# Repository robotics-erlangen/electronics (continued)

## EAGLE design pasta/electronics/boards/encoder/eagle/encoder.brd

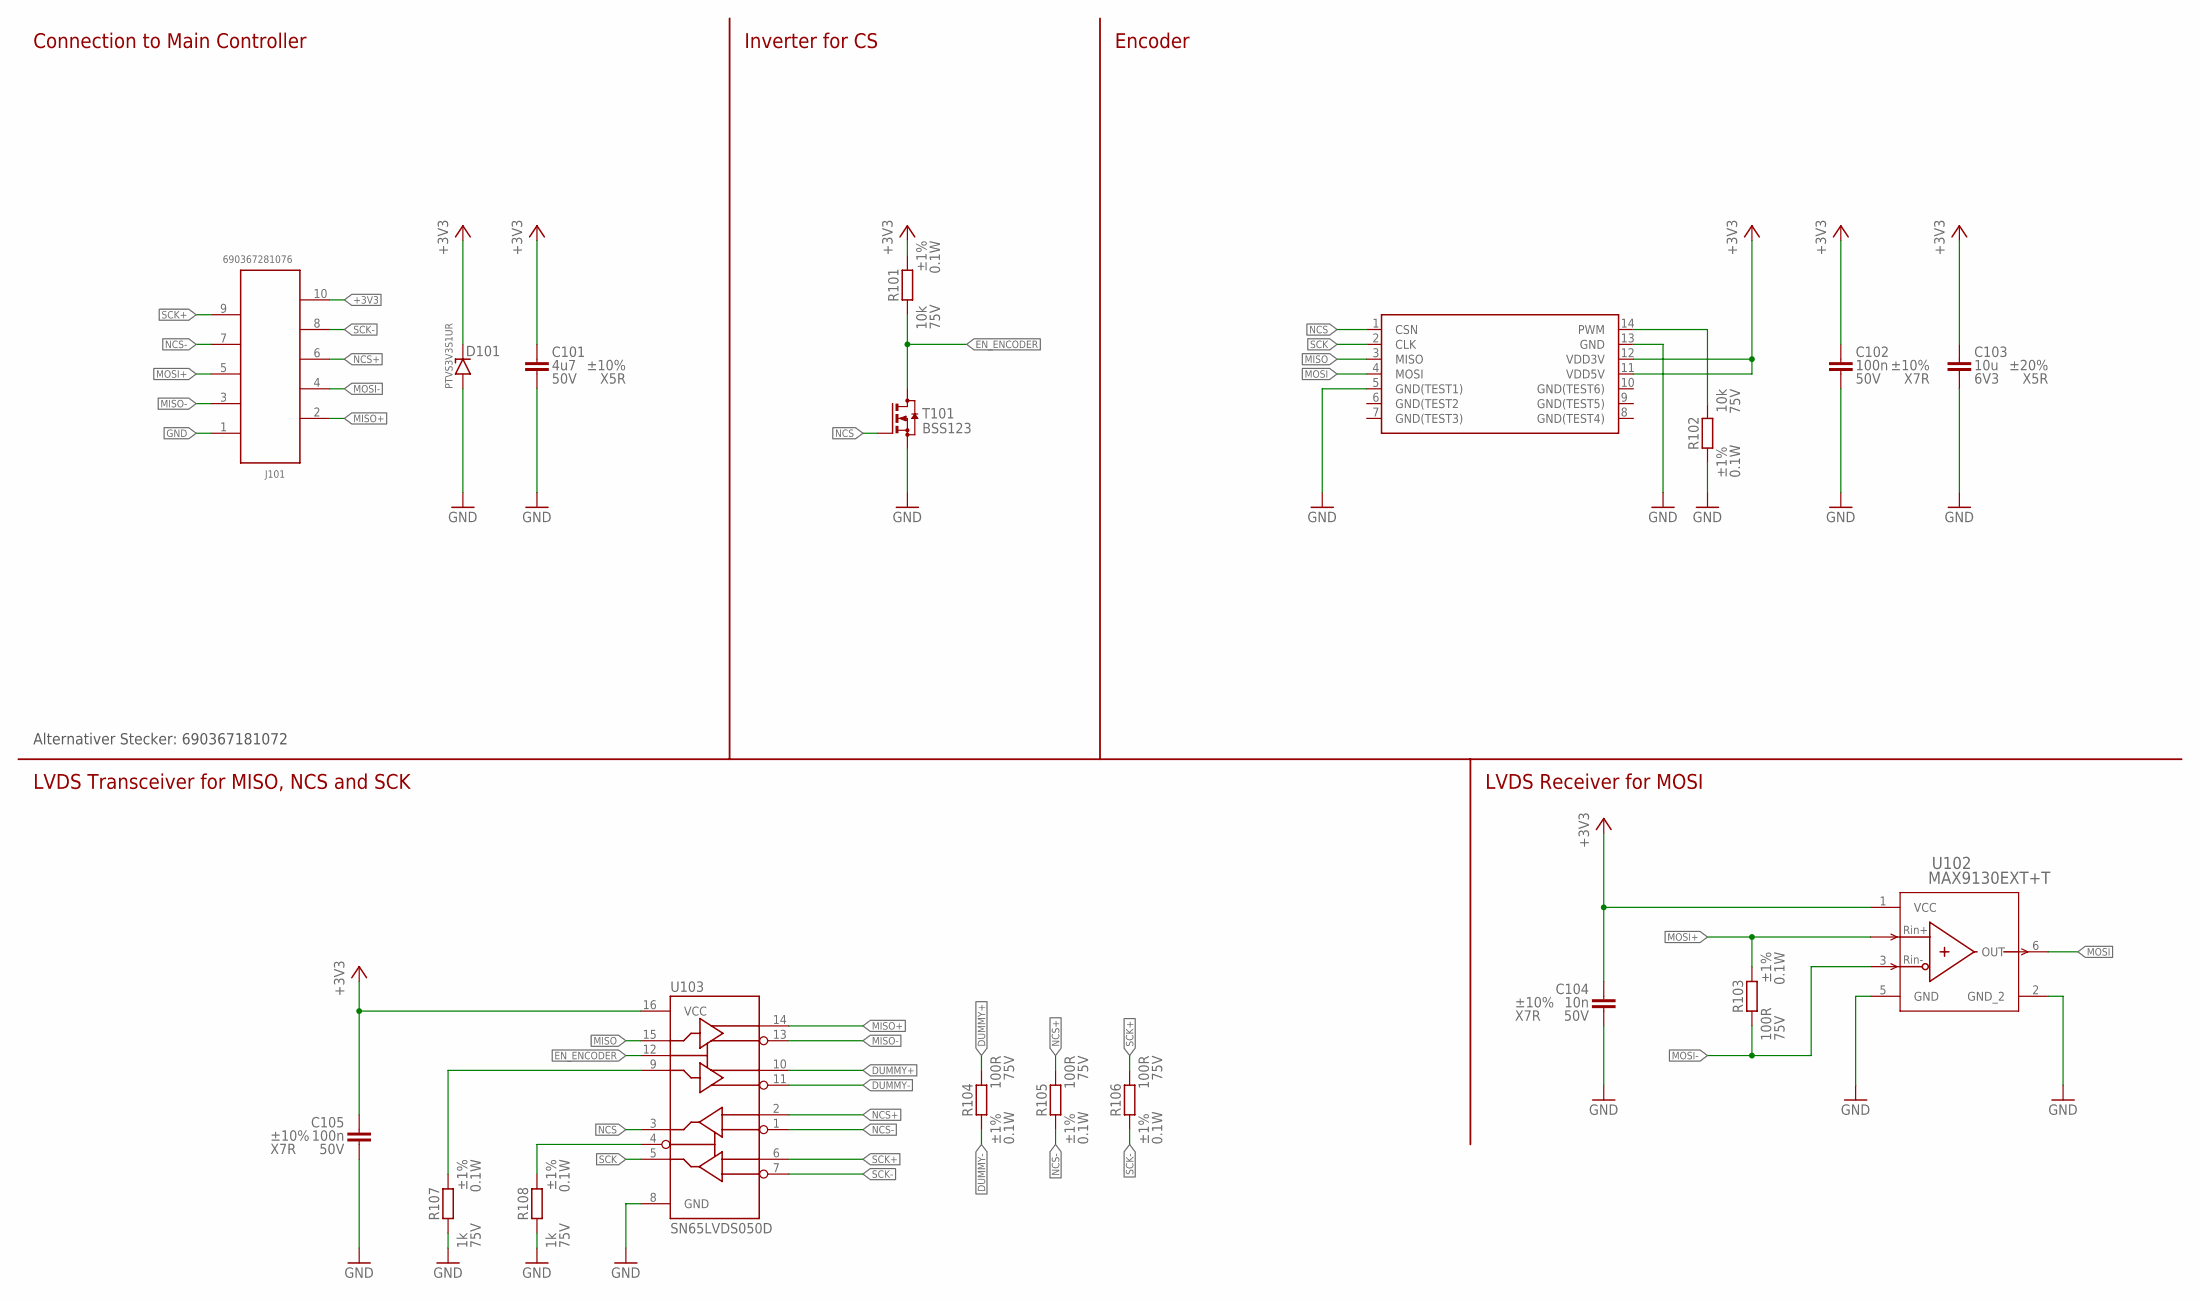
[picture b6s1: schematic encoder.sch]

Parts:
C101: 4u7 6V3; C0805
C102, C105: 100n 6V3; C0603
C103: 10u 6V3; C0603
C104: 10n 50V; C0603
D101: PTVS3V3S1UR; SOD123
J101: 690367281076; MPN 690367281076
R101, R102: 10k; R0603
R103, R104, R105, R106: 100R; R0603
R107, R108: 1k; R0603
T101: BSS123; SOT23-3
U101: AS5048A-HTSP
U102: MAX9130EXT+T; 21-0077G_MXM
U103: SN65LVDS050D; SOIC-16

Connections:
+3V3: C101.1, C102.1, C103.1, C104.1, C105.1, D101.C (KATHODE), J101.10 (1), R101.2, U101.11 (VDD5V), U101.12 (VDD3V), U102.1 (VCC), U103.16 (VCC)
DUMMY+: R104.1, U103.10 (2Y)
DUMMY-: R104.2, U103.11 (2Z)
EN_ENCODER: R101.1, T101.3 (D), U103.12 (DE)
GND: C101.2, C102.2, C103.2, C104.2, C105.2, D101.A (ANODE), J101.1 (10), R102.2, R107.1, R108.1, T101.2 (S), U101.5 (GND(TEST1)), U101.13 (GND), U102.2 (GND_2), U102.5 (GND), U103.8 (GND)
MISO: U101.3 (MISO), U103.15 (1D)
MISO+: J101.2 (9), U103.14 (1Y)
MISO-: J101.3 (8), U103.13 (1Z)
MOSI: U101.4 (MOSI), U102.6 (OUT)
MOSI+: J101.5 (6), R103.2, U102.4 (IN+)
MOSI-: J101.4 (7), R103.1, U102.3 (IN-)
unnamed: R102.1, U101.14 (PWM)
unnamed: R108.2, U103.4 (RE)
unnamed: R107.2, U103.9 (2D)
NCS: T101.1 (G), U101.1 (CSN), U103.3 (1R)
NCS+: J101.6 (5), R105.1, U103.2 (1A)
NCS-: J101.7 (4), R105.2, U103.1 (1B)
SCK: U101.2 (CLK), U103.5 (2R)
SCK+: J101.9 (2), R106.1, U103.6 (2A)
SCK-: J101.8 (3), R106.2, U103.7 (2B)

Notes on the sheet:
Alternativer Stecker: 690367181072
Connection to Main Controller
Inverter for CS
Encoder
LVDS Transceiver for MISO, NCS and SCK
LVDS Receiver for MOSI

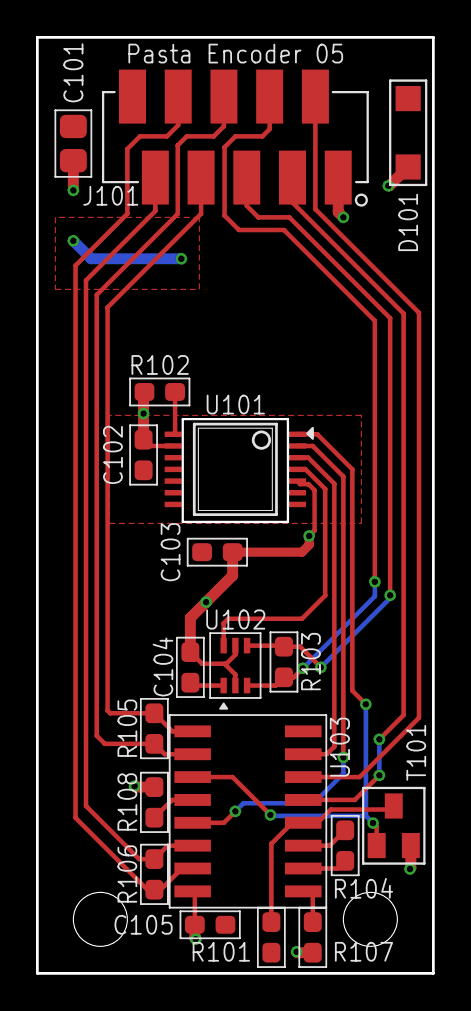
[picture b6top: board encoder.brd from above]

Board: 2 copper layers, 22.0 x 52.0 mm, 19 parts (0 on the bottom side), 20 nets.

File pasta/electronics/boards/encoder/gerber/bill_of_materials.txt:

Stückliste exportiert aus D:/hardware/pasta/electronics/boards/encoder/eagle/encoder.sch am 04.07.2023 16:03

Part Value        Device                Package      Description                                                                                      CAPACITANCE COPYRIGHT                                                DIELECTRIC MF                        MOUSER               MPN               POWER RESISTANCE TOLERANCE VOLTAGE
C101 4u7 6V3      C(4.7UF,50V,0805)     C0805        Robotics Erlangen Capacitor Library                                                              4u7                                                                  X5R        Samsung                                        CL21A475KBQNNNE                    ±10%      50V    
C102 100n 6V3     C(100NF,50V,0603)     C0603        Robotics Erlangen Capacitor Library                                                              100n                                                                 X7R        Würth Elektronik                               885012206095                       ±10%      50V    
C103 10u 6V3      C(10UF,6.3V,0603)     C0603        Robotics Erlangen Capacitor Library                                                              10u                                                                  X5R        Würth Elektronik                               885012106006                       ±20%      6V3    
C104 10n 50V      C(10NF,50V,0603)      C0603        Robotics Erlangen Capacitor Library                                                              10n                                                                  X7R        Würth Elektronik                               885012206089                       ±10%      50V    
C105 100n 6V3     C(100NF,50V,0603)     C0603        Robotics Erlangen Capacitor Library                                                              100n                                                                 X7R        Würth Elektronik                               885012206095                       ±10%      50V    
D101 PTVS3V3S1UR  PTVS3V3S1UR           SOD123                                                                                                                                                                                        Nexperia                  771-PTVS3V3S1UR115    PTVS3V3S1UR,115                                    
J101 690367281076 690367281076          690367281076 WR-MM Female SMT Connector with Polarization, 10 Pins=>Code : Con_BTB_MM_Female_SMT_690367281076                                                                                 Würth Elektronik                               690367281076                                        
R101 10k          R(10K,75V,0.1W,0603)  R0603        Robotics Erlangen Resistor Library                                                                                                                                               YAGEO                                          RC0603FR-0710KL   0.1W  10k        ±1%       75V    
R102 10k          R(10K,75V,0.1W,0603)  R0603        Robotics Erlangen Resistor Library                                                                                                                                               YAGEO                                          RC0603FR-0710KL   0.1W  10k        ±1%       75V    
R103 100R         R(100R,75V,0.1W,0603) R0603        Robotics Erlangen Resistor Library                                                                                                                                               YAGEO                                          RC0603FR-07100RL  0.1W  100R       ±1%       75V    
R104 100R         R(100R,75V,0.1W,0603) R0603        Robotics Erlangen Resistor Library                                                                                                                                               YAGEO                                          RC0603FR-07100RL  0.1W  100R       ±1%       75V    
R105 100R         R(100R,75V,0.1W,0603) R0603        Robotics Erlangen Resistor Library                                                                                                                                               YAGEO                                          RC0603FR-07100RL  0.1W  100R       ±1%       75V    
R106 100R         R(100R,75V,0.1W,0603) R0603        Robotics Erlangen Resistor Library                                                                                                                                               YAGEO                                          RC0603FR-07100RL  0.1W  100R       ±1%       75V    
R107 1k           R(1.0K,75V,0.1W,0603) R0603        Robotics Erlangen Resistor Library                                                                                                                                               YAGEO                                          RC0603FR-071KL    0.1W  1k         ±1%       75V    
R108 1k           R(1.0K,75V,0.1W,0603) R0603        Robotics Erlangen Resistor Library                                                                                                                                               YAGEO                                          RC0603FR-071KL    0.1W  1k         ±1%       75V    
T101 BSS123       BSS123                SOT23-3      N-CHANNEL MOS FET                                                                                                                                                                Nexperia                  726-BSS123NH6327XTSA BSS123NH6327XTSA1                                   
U101 AS5048A-HTSP AS5048A-HTSP          AS5048A-HTSP                                                                                                                                                                                  ams                       985-AS5048A-HTSP-500 AS5048A-HTSP                                        
U102 MAX9130EXT+T MAX9130EXT+T          21-0077G_MXM                                                                                                              Copyright (C) 2021 Ultra Librarian. All rights reserved.            Maxim Integrated Products                      MAX9130EXT+T                                        
U103 SN65LVDS050D SN65LVDS050D          SOIC-16                                                                                                                                                                                       Texas Instruments                              SN65LVDS050D

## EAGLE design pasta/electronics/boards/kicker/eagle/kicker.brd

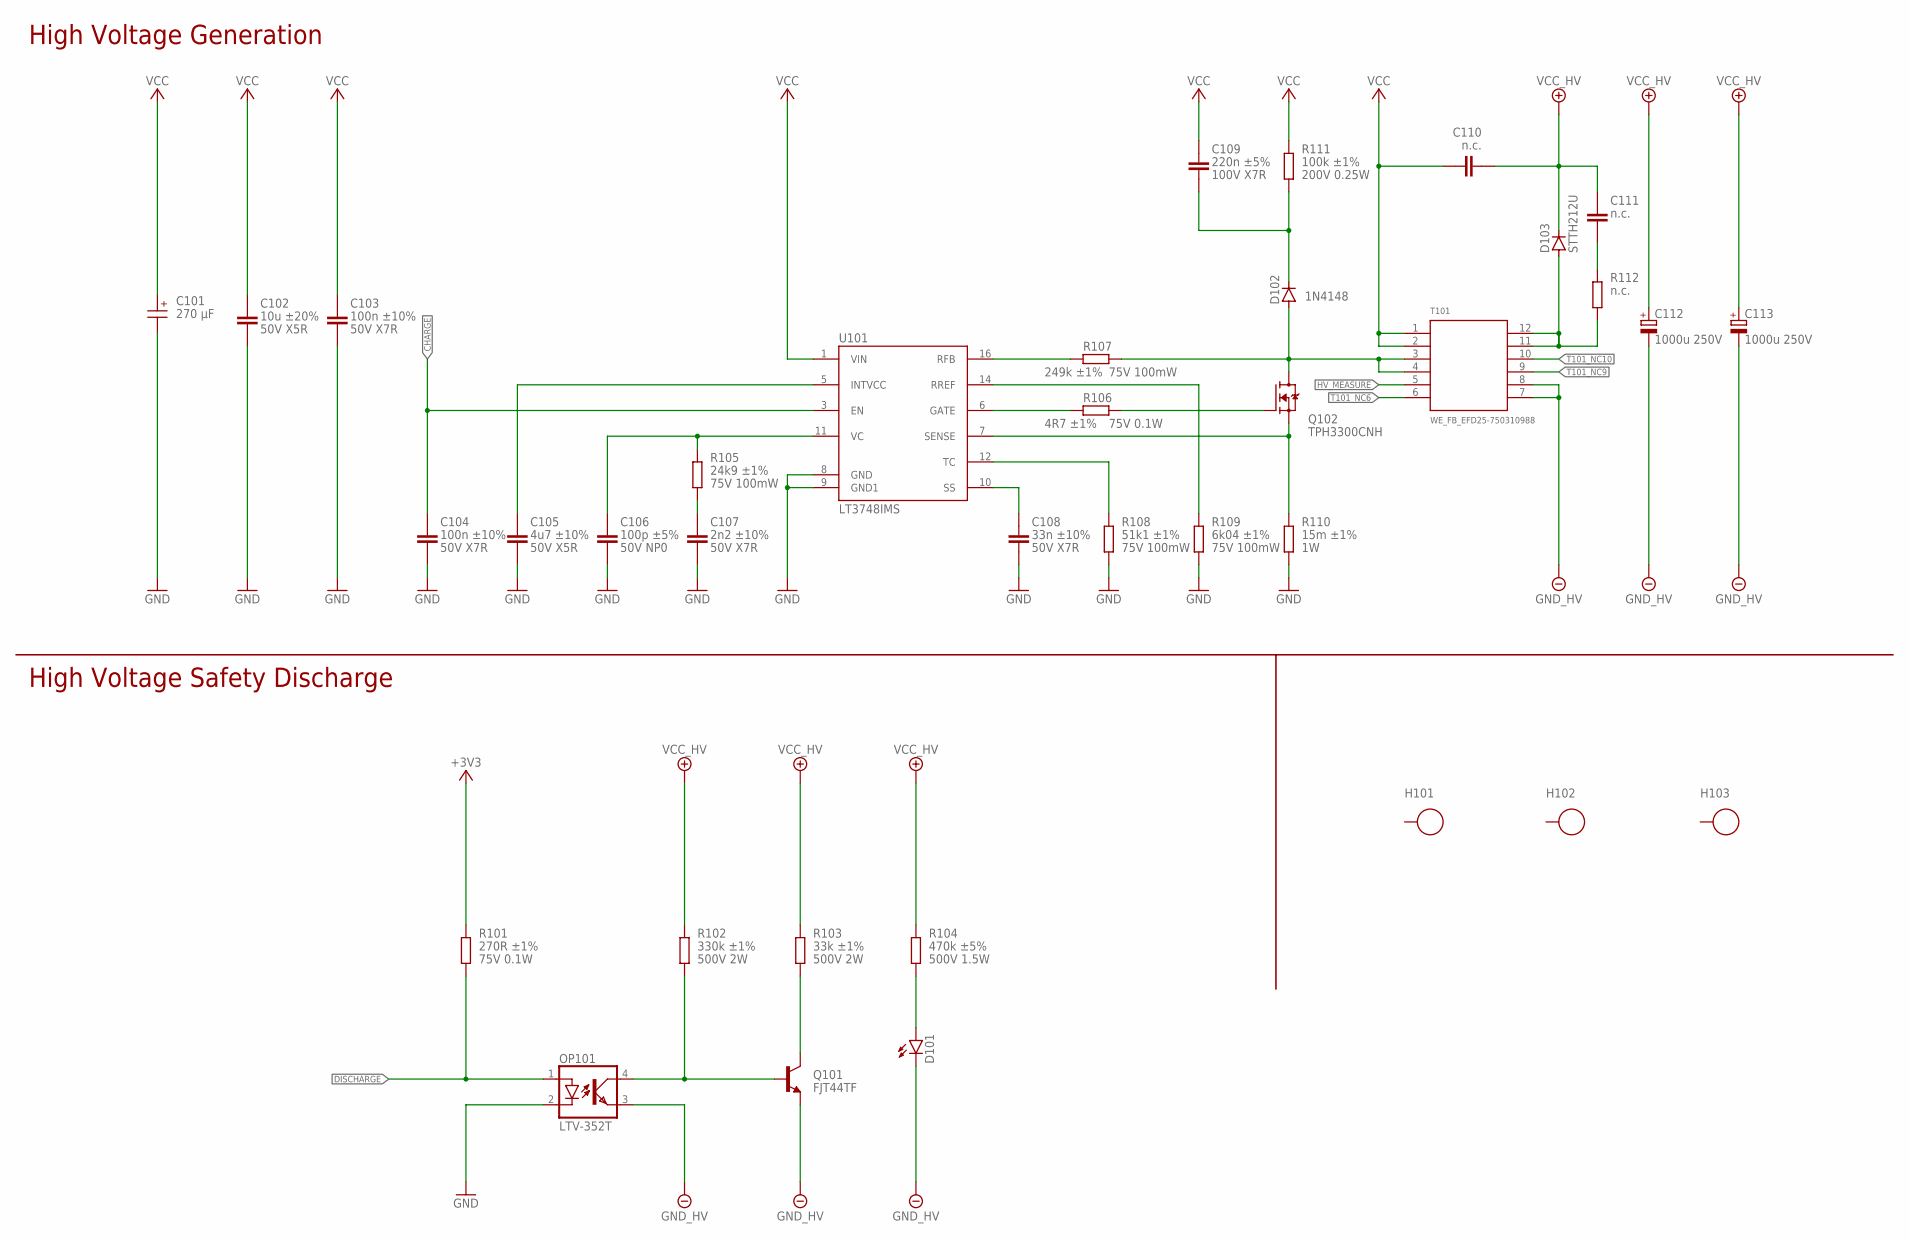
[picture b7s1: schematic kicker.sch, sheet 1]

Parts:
C101: 270 µF; WCAP-PSLC_10X12.4(DXL)
C102: 10u ±20% 50V X5R; C1206
C103, C104: 100n ±10% 50V X7R; C0603
C105: 4u7 ±10% 50V X5R; C0805
C106: 100p ±5% 50V NP0; C0603
C107: 2n2 ±10% 50V X7R; C0603
C108: 33n ±10% 50V X7R; C0603
C109: C(1210); C1210; TOLERANCE ±5%; VOLTAGE 100V; MPN C0805C224J1RECTU
C110, C111: n.c.; C1206
C112, C113: 1000u 250V; ESMQ251VSN102MQ45S
D101: LED5MM
D102: 1N4148; SOD-123
D103: STTH212U; SMB
H101, H102, H103: 9774060360R; 9774***360
OP101: LTV-352T; DIL4-SMD
Q101: FJT44TF; SOT223
Q102: TPH3300CNH; SOP-8
R101: 270R ±1% 75V 0.1W; R0603
R102: R(2512); R2512; TOLERANCE ±1%; VOLTAGE 500V; MPN CRGP2512F330K
R103: R(2512); R2512; TOLERANCE 1%; VOLTAGE 500V; MPN CRGP2512F33K
R104: R(2512); R2512; TOLERANCE ±5%; VOLTAGE 500V; MPN CRCW2512470KJNEGHP
R105: R(0603); R0603; TOLERANCE ±1%; VOLTAGE 75V; MPN RE0603FRE0724K9L
R106: 4R7 ±1% 75V 0.1W; R0603
R107: R(0603); R0603; TOLERANCE ±1%; VOLTAGE 75V; MPN RC0603FR-07249KL
R108: R(0603); R0603; TOLERANCE ±1%; VOLTAGE 75V; MPN RC0603FR-0751K1L
R109: R(0603); R0603; TOLERANCE ±1%; VOLTAGE 75V; MPN AC0603FR-136K04L
R110: R(1206); R1206; TOLERANCE ±1%; MPN ERJ-8BWFR015V
R111: 100k ±1% 200V 0.25W; R1206
R112: n.c.; R1206
T101: WE_FB_EFD25-750310988; WE_FB_EFD25
U101: LT3748IMS; MSOP16

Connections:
+3V3: R101.2; also elsewhere on the board
CHARGE: C104.1, U101.3 (EN); also elsewhere on the board
DISCHARGE: OP101.1 (A), R101.1; also elsewhere on the board
GND: C101.2 (-), C102.2, C103.2, C104.2, C105.2, C106.2, C107.2, C108.2, OP101.2 (C), R108.1, R109.1, R110.1, U101.8 (GND), U101.9 (GND1); also elsewhere on the board
GND_HV: C112.N (-), C113.N (-), D101.K (C), OP101.3 (EMIT), Q101.3 (E), T101.7, T101.8; also elsewhere on the board
HV_MEASURE: T101.5
unnamed: R108.2, U101.12 (TC)
unnamed: D103.A, R112.1, T101.11, T101.12
unnamed: R109.2, U101.14 (RREF)
unnamed: C108.1, U101.10 (SS)
unnamed: D101.A, R104.1
unnamed: C109.2, D102.C, R111.1
unnamed: Q102.1 (S), Q102.2 (S), Q102.3 (S), R110.2, U101.7 (SENSE)
unnamed: C105.1, U101.5 (INTVCC)
unnamed: C106.1, R105.2, U101.11 (VC)
unnamed: C107.1, R105.1
unnamed: Q102.4 (G), R106.1
unnamed: R106.2, U101.6 (GATE)
unnamed: R107.2, U101.16 (RFB)
unnamed: C111.2, R112.2
unnamed: OP101.4 (COL), Q101.1 (B), R102.1
unnamed: Q101.2 (C), Q101.4 (C), R103.1
T101_NC6: T101.6
T101_NC9: T101.9
T101_NC10: T101.10
TRAFO: D102.A, Q102.5 (D), R107.1, T101.3, T101.4
VCC: C101.1 (+), C102.1, C103.1, C109.1, C110.1, R111.2, T101.1, T101.2, U101.1 (VIN); also elsewhere on the board
VCC_HV: C110.2, C111.1, C112.P (+), C113.P (+), D103.C, R102.2, R103.2, R104.2; also elsewhere on the board

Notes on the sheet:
High Voltage Generation
High Voltage Safety Discharge

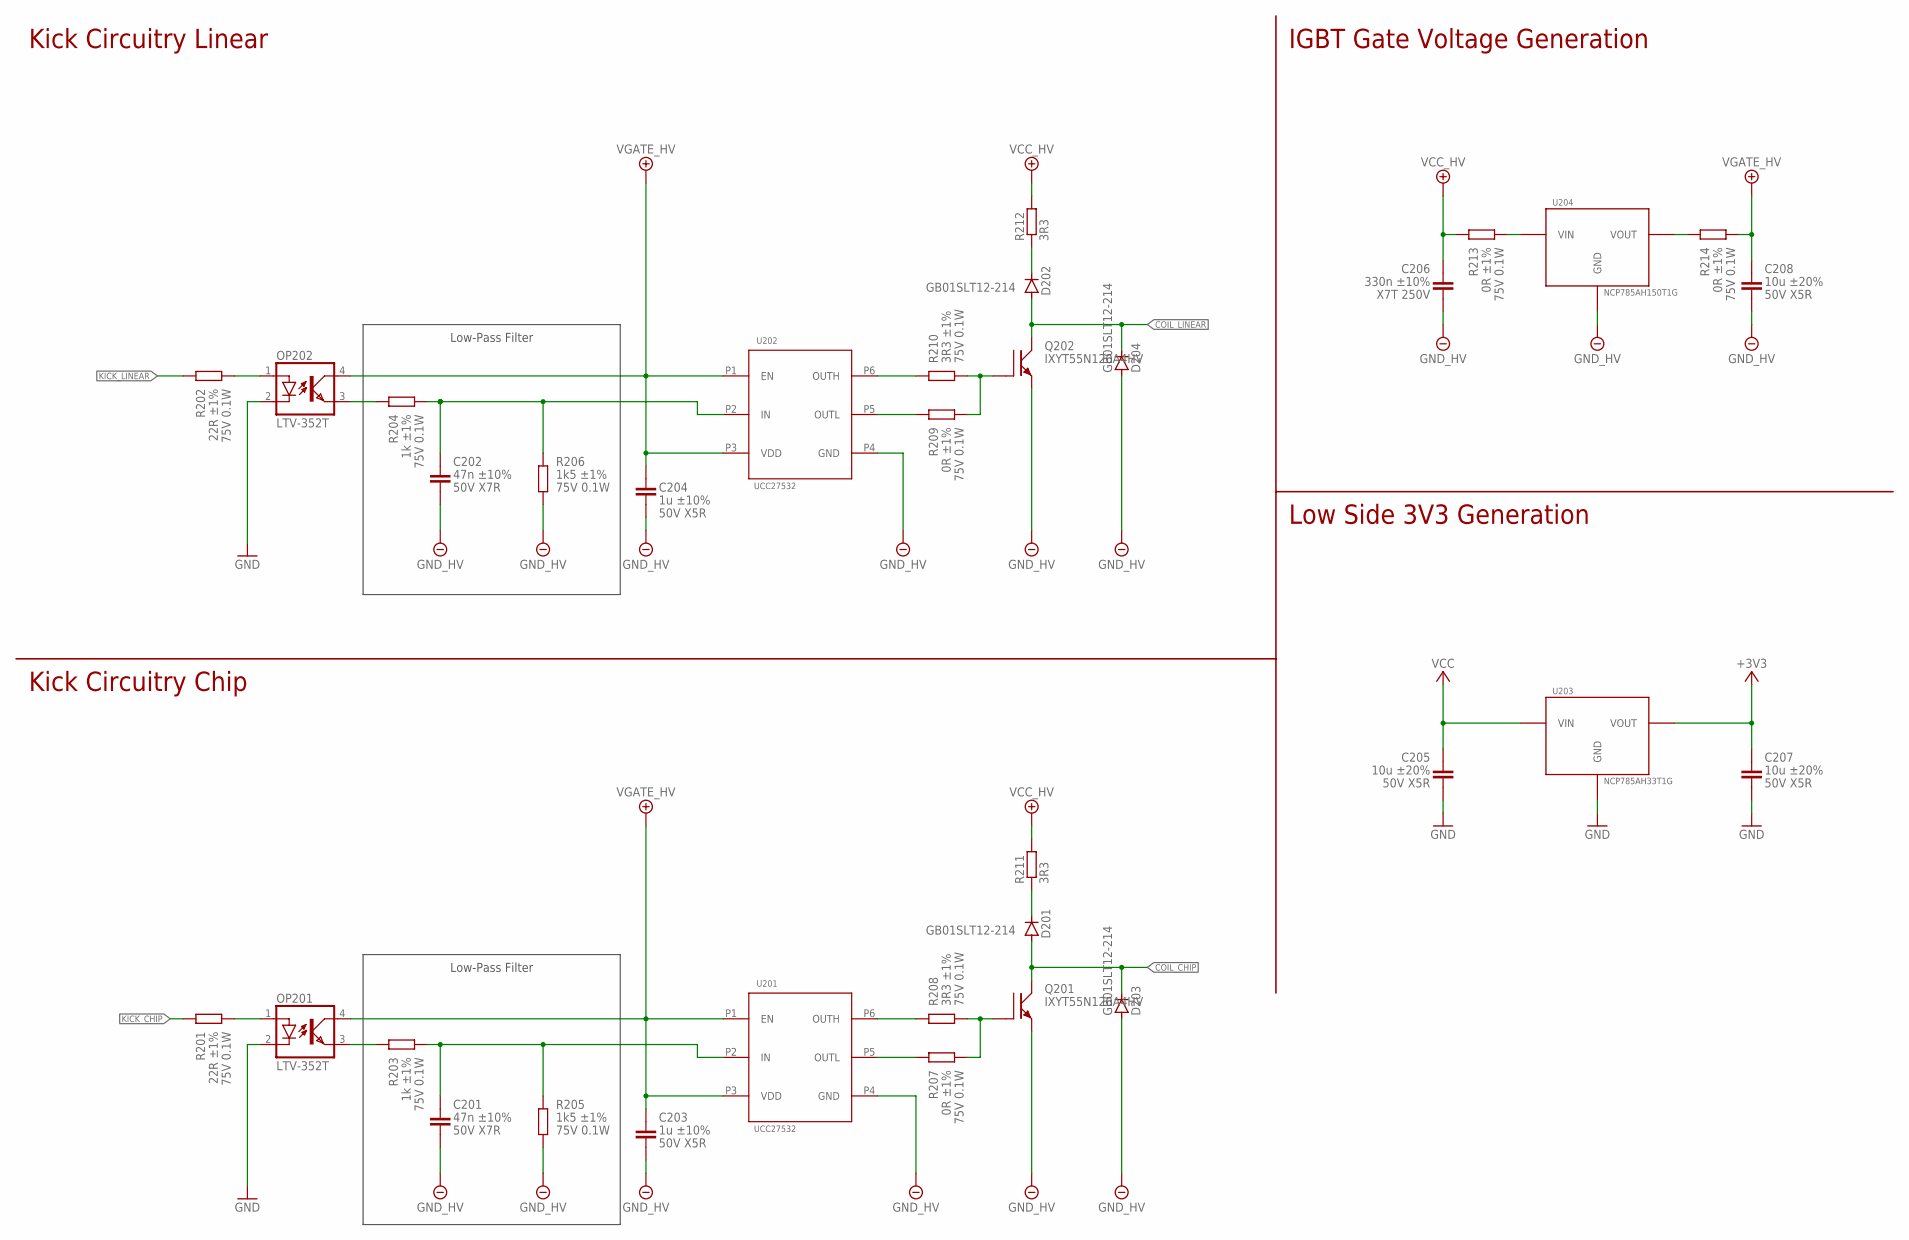
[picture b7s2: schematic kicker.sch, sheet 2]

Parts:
C201, C202: 47n ±10% 50V X7R; C0603
C203, C204: 1u ±10% 50V X5R; C0603
C205, C207, C208: 10u ±20% 50V X5R; C1206
C206: C(1210); C1210; TOLERANCE ±10%; VOLTAGE 250V; MPN C3225X7T2E334K200AA
D201, D202, D203, D204: GB01SLT12-214; DO-214
OP201, OP202: LTV-352T; DIL4-SMD
Q201, Q202: IXYT55N120A4HV; TO-268HV
R201, R202: 22R ±1% 75V 0.1W; R0603
R203, R204: 1k ±1% 75V 0.1W; R0603
R205, R206: 1k5 ±1% 75V 0.1W; R0603
R207, R209, R213, R214: 0R ±1% 75V 0.1W; R0603
R208, R210: 3R3 ±1% 75V 0.1W; R0603
R211, R212: 3R3; R4527
U201, U202: UCC27532; SOT23-6
U203: NCP785AH33T1G; NCP785AH*T1G
U204: NCP785AH150T1G; NCP785AH*T1G

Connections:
+3V3: C207.1, U203.3 (VOUT); also elsewhere on the board
COIL_CHIP: D201.A, D203.C, Q201.3 (C); also elsewhere on the board
COIL_LINEAR: D202.A, D204.C, Q202.3 (C); also elsewhere on the board
GND: C205.2, C207.2, OP201.2 (C), OP202.2 (C), U203.2 (GND); also elsewhere on the board
GND_HV: C201.2, C202.2, C203.2, C204.2, C206.2, C208.2, D203.A, D204.A, Q201.1 (E), Q202.1 (E), R205.1, R206.1, U201.P4 (GND), U202.P4 (GND), U204.2 (GND); also elsewhere on the board
KICK_CHIP: R201.1; also elsewhere on the board
KICK_LINEAR: R202.1; also elsewhere on the board
unnamed: OP202.3 (EMIT), R204.1
unnamed: OP201.3 (EMIT), R203.1
unnamed: R213.2, U204.1 (VIN)
unnamed: R214.1, U204.3 (VOUT)
unnamed: R208.1, U201.P6 (OUTH)
unnamed: R210.1, U202.P6 (OUTH)
unnamed: R209.1, U202.P5 (OUTL)
unnamed: Q202.2 (G), R209.2, R210.2
unnamed: C202.1, R204.2, R206.2, U202.P2 (IN)
unnamed: R207.1, U201.P5 (OUTL)
unnamed: Q201.2 (G), R207.2, R208.2
unnamed: D202.C, R212.1
unnamed: OP201.1 (A), R201.2
unnamed: D201.C, R211.1
unnamed: C201.1, R203.2, R205.2, U201.P2 (IN)
unnamed: OP202.1 (A), R202.2
VCC: C205.1, U203.1 (VIN); also elsewhere on the board
VCC_HV: C206.1, R211.2, R212.2, R213.1; also elsewhere on the board
VGATE_HV: C203.1, C204.1, C208.1, OP201.4 (COL), OP202.4 (COL), R214.2, U201.P1 (EN), U201.P3 (VDD), U202.P1 (EN), U202.P3 (VDD); also elsewhere on the board

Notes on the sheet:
Kick Circuitry Linear
Kick Circuitry Chip
Low Side 3V3 Generation
IGBT Gate Voltage Generation
Low-Pass Filter

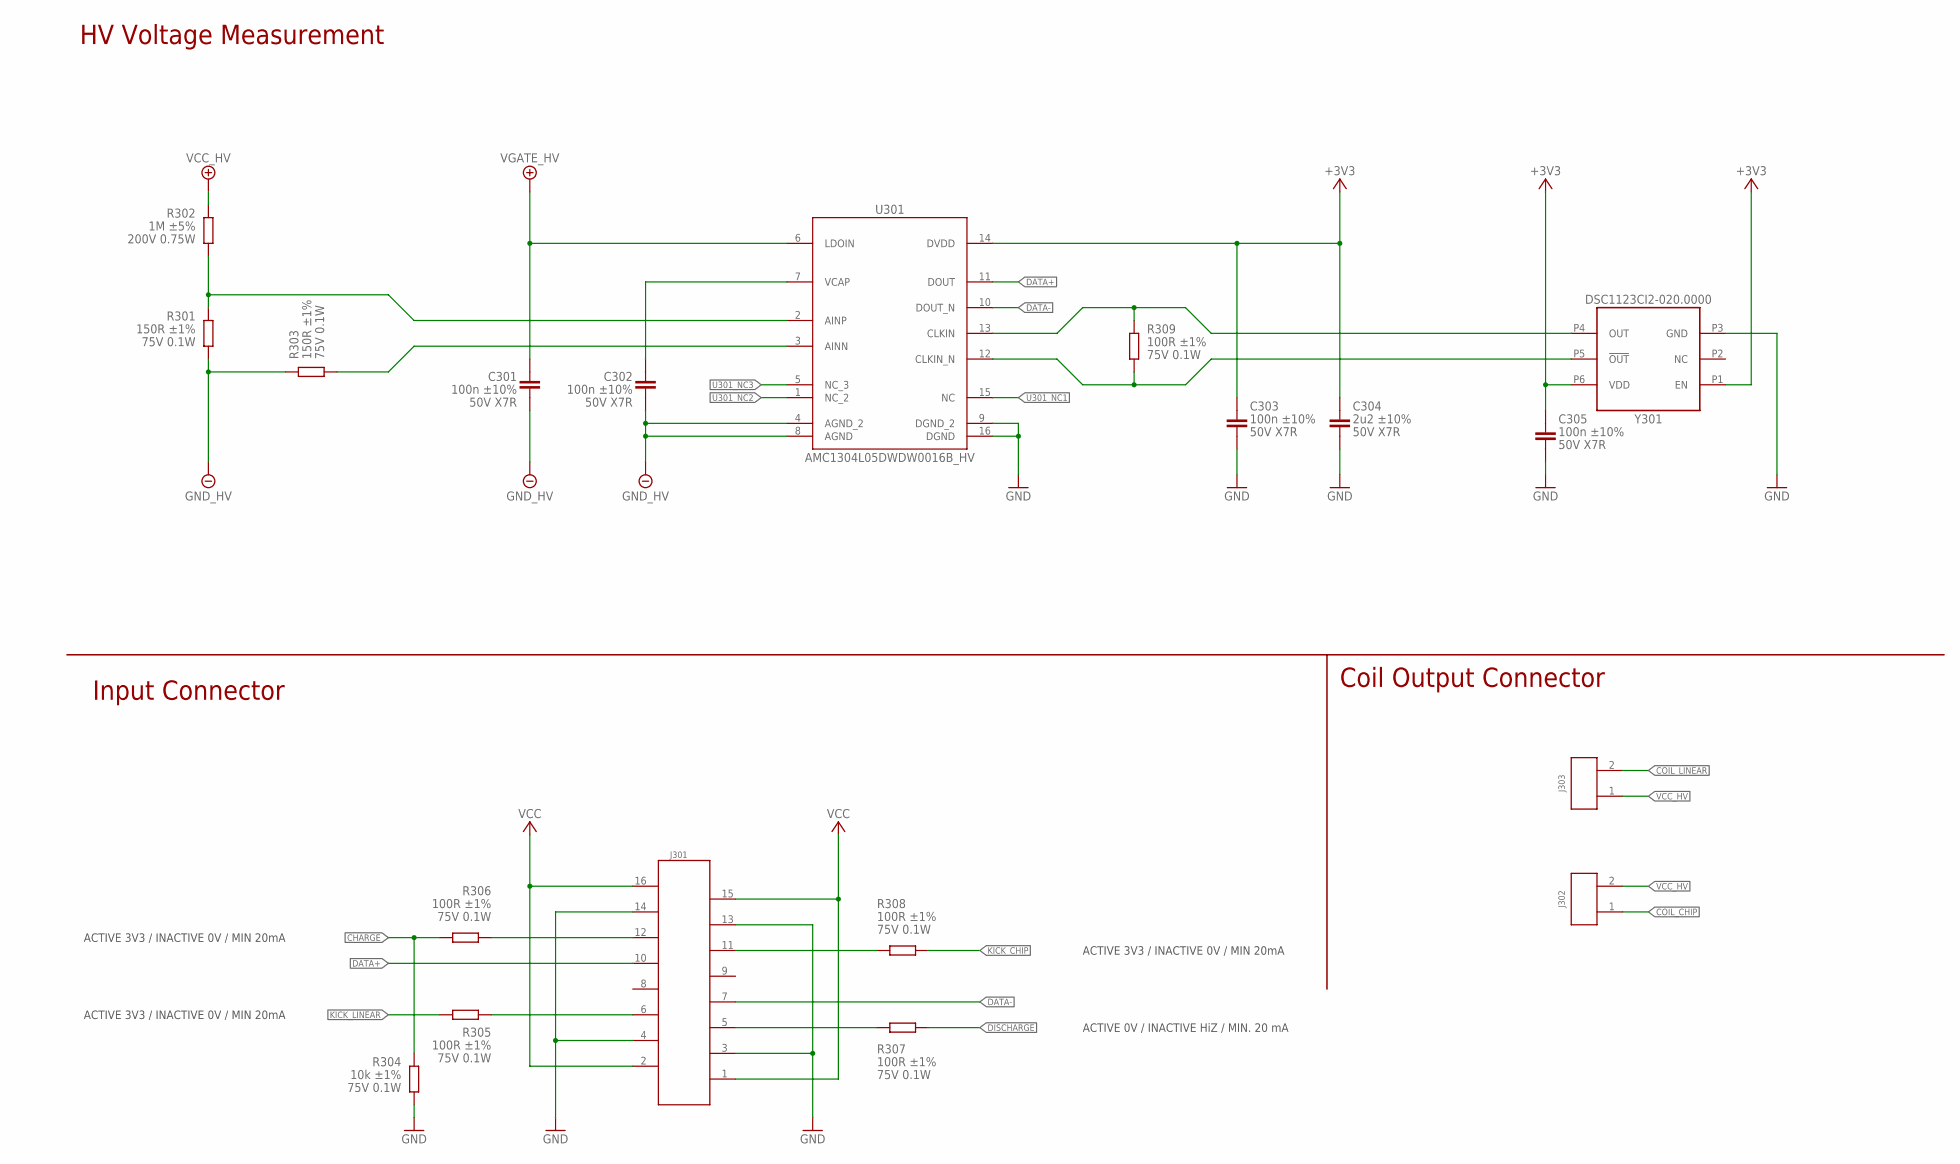
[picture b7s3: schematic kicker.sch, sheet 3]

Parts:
C301, C302, C303, C305: 100n ±10% 50V X7R; C0603
C304: 2u2 ±10% 50V X7R; C0805
J301: 690367181672
J302, J303: 66100311622; 66100311622*
R301, R303: 150R ±1% 75V 0.1W; R0603
R302: R(2010); R2010; TOLERANCE ±5%; VOLTAGE 200V; MPN RC2010JK-071ML
R304: 10k ±1% 75V 0.1W; R0603
R305, R306, R307, R308, R309: 100R ±1% 75V 0.1W; R0603
U301: AMC1304L05DWDW0016B_HV; DW0016B_HV
Y301: DSC1123CI2-020.0000; DSC11X3

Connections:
+3V3: C303.1, C304.1, C305.1, U301.14 (DVDD), Y301.P1 (EN), Y301.P6 (VDD); also elsewhere on the board
CHARGE: R304.2, R306.2; also elsewhere on the board
CLK-: R309.1, U301.12 (CLKIN_N), Y301.P5 (!OUT)
COIL_CHIP: J302.1; also elsewhere on the board
COIL_LINEAR: J303.2; also elsewhere on the board
DATA+: J301.10 (7), U301.11 (DOUT)
DATA-: J301.7 (10), U301.10 (DOUT_N)
DISCHARGE: R307.2; also elsewhere on the board
GND: C303.2, C304.2, C305.2, J301.3 (14), J301.4 (13), J301.13 (4), J301.14 (3), R304.1, U301.9 (DGND_2), U301.16 (DGND), Y301.P3 (GND); also elsewhere on the board
GND_HV: C301.2, C302.2, R301.1, R303.2, U301.4 (AGND_2), U301.8 (AGND); also elsewhere on the board
KICK_CHIP: R308.1; also elsewhere on the board
KICK_LINEAR: R305.2; also elsewhere on the board
unnamed: R309.2, U301.13 (CLKIN), Y301.P4 (OUT)
unnamed: R301.2, R302.1, U301.2 (AINP)
unnamed: R303.1, U301.3 (AINN)
unnamed: J301.12 (5), R306.1
unnamed: J301.6 (11), R305.1
unnamed: J301.5 (12), R307.1
unnamed: C302.1, U301.7 (VCAP)
unnamed: J301.11 (6), R308.2
U301_NC1: U301.15 (NC)
U301_NC2: U301.1 (NC_2)
U301_NC3: U301.5 (NC_3)
VCC: J301.1 (16), J301.2 (15), J301.15 (2), J301.16 (1); also elsewhere on the board
VCC_HV: J302.2, J303.1, R302.2; also elsewhere on the board
VGATE_HV: C301.1, U301.6 (LDOIN); also elsewhere on the board

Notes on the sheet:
Input Connector
Coil Output Connector
HV Voltage Measurement
ACTIVE 0V / INACTIVE HiZ / MIN. 20 mA
ACTIVE 3V3 / INACTIVE 0V / MIN 20mA
